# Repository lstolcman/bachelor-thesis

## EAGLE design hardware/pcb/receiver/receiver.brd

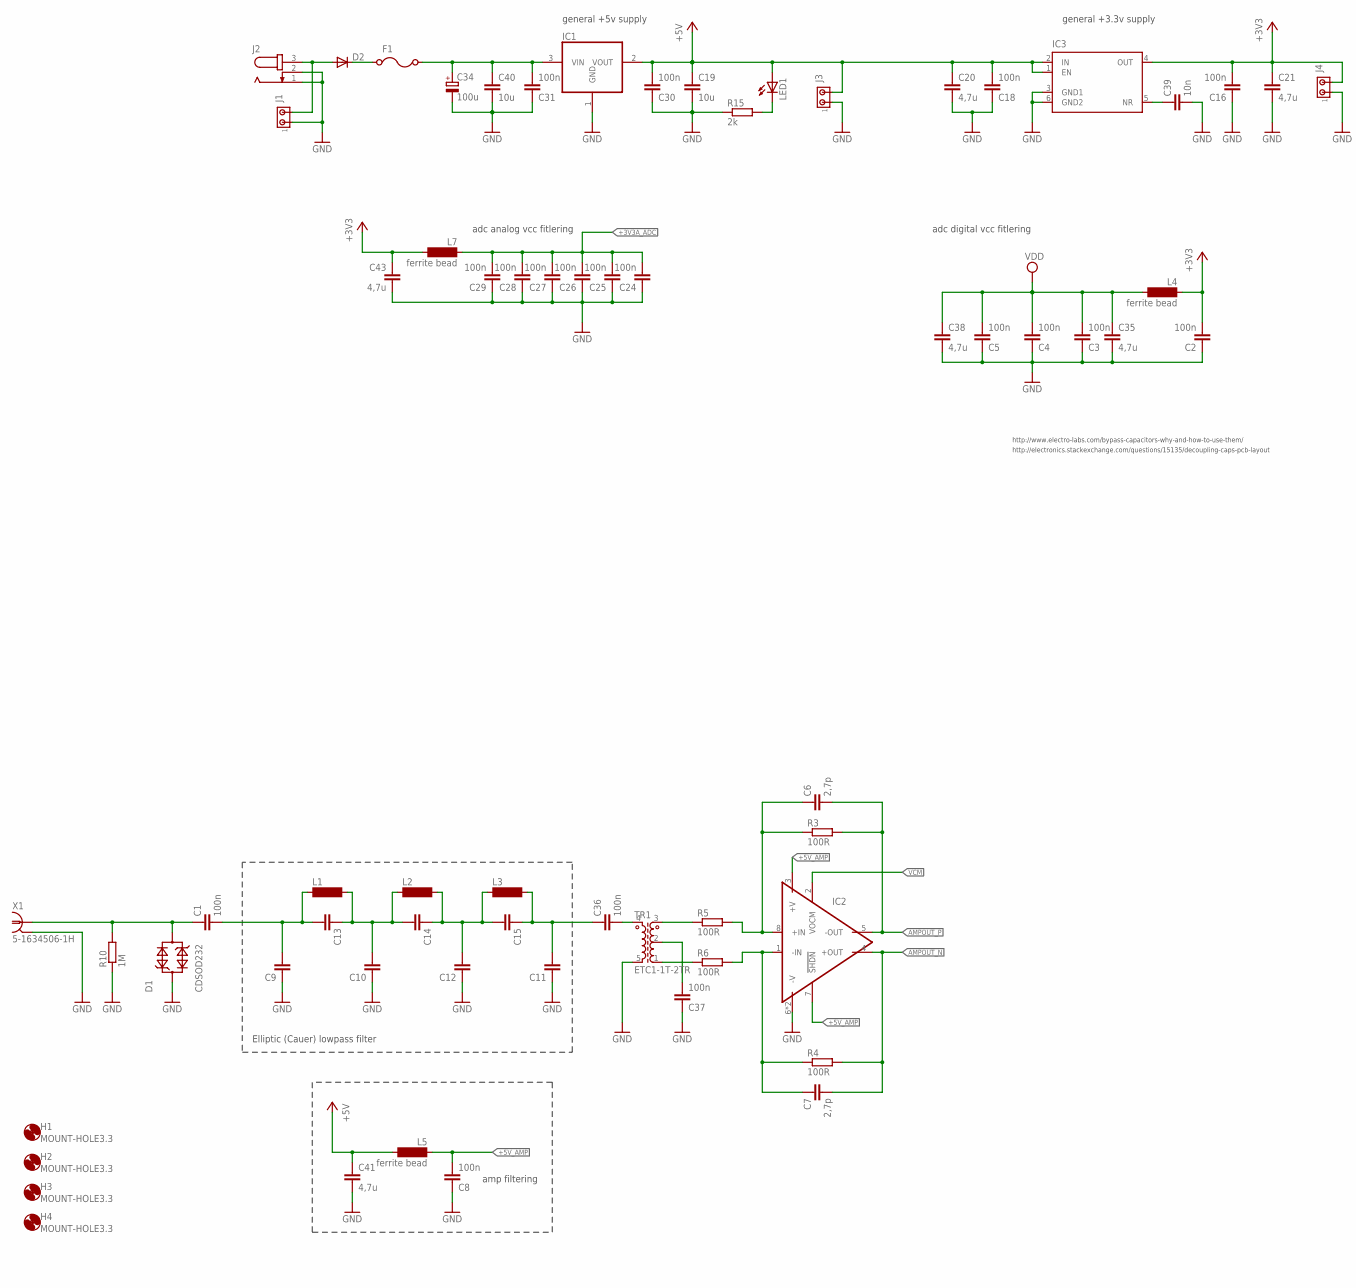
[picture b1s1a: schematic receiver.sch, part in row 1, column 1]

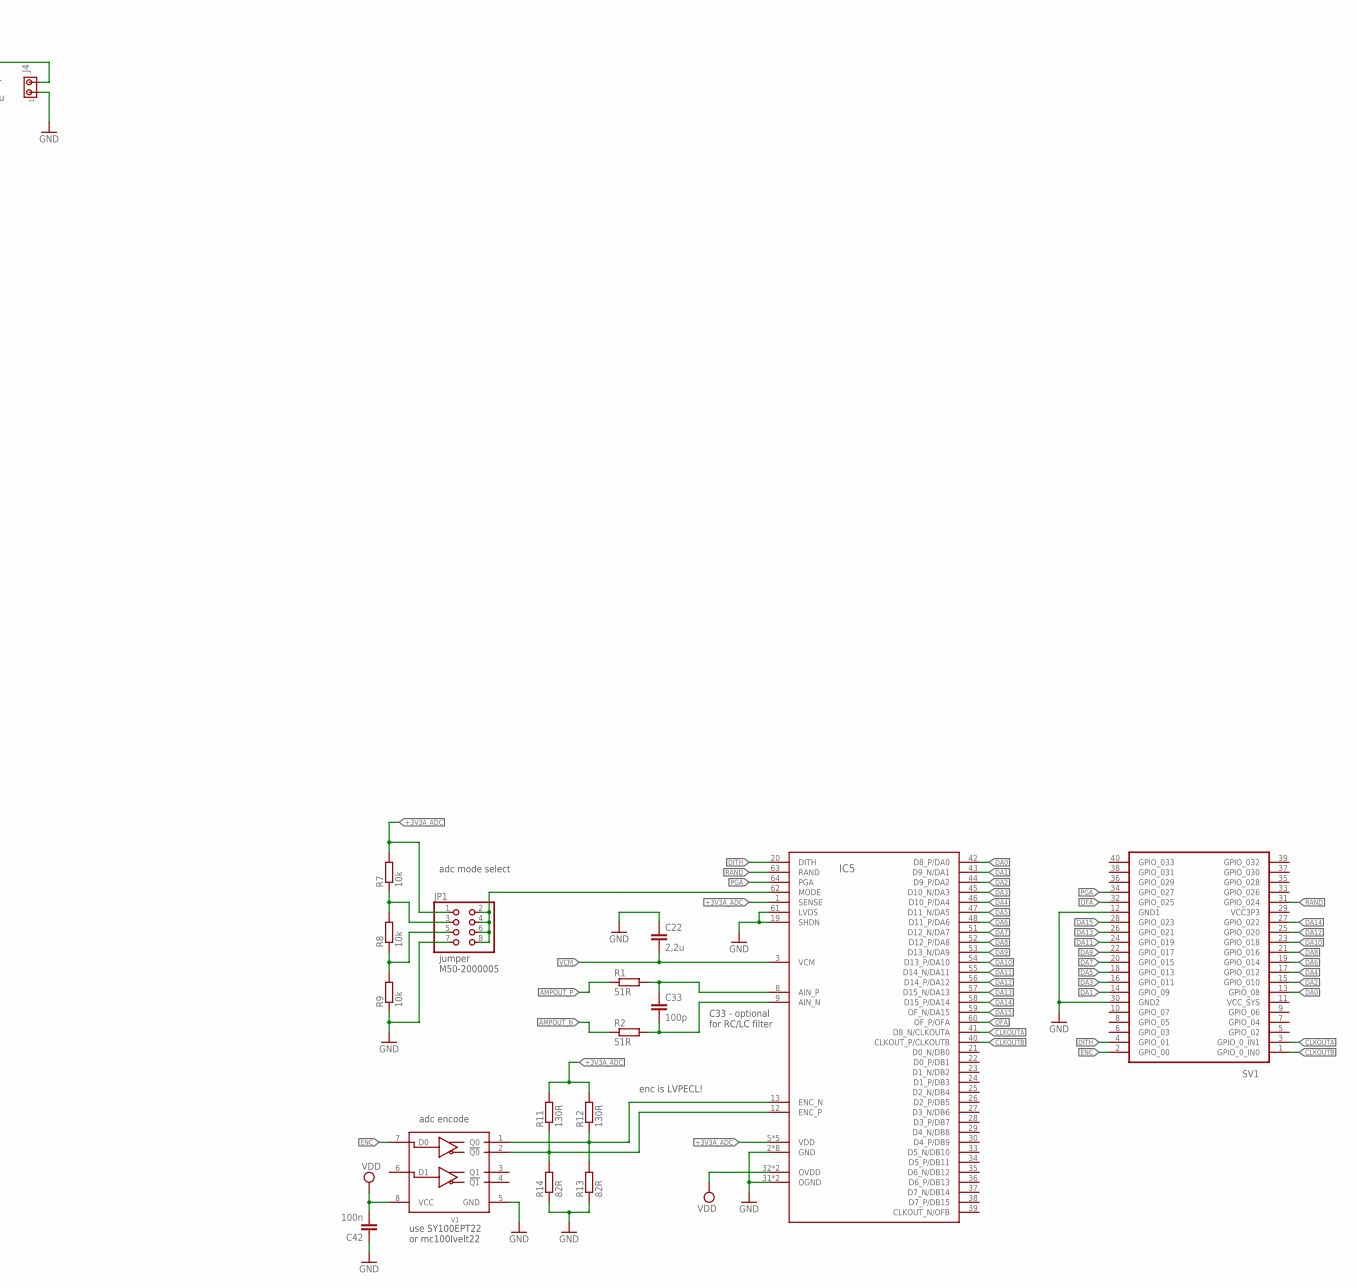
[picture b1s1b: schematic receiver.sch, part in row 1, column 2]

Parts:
C1, C2, C3, C4, C5, C8, C16, C18, C24, C25, C26, C27, C28, C29, C30, C31, C36, C37, C42: 100n; C0805
C6, C7: 2,7p; C0805
C9, C10, C11, C12, C13, C14, C15: C-EUC0805; C0805
C19, C40: 10u; C0805
C20, C21, C35, C38, C41, C43: 4,7u; C0805
C22: 2,2u; C0805
C33: 100p; C0805
C34: 100u; 153CLV-0605
C39: 10n; C0805
D1: CDSOD232; SOD323
D2: DIODE-DO214AC; DO214AC
F1: 0ZCG0150BF2C; CN1812
H1, H2, H3, H4: MOUNT-HOLE3.3; 3,3
IC1: REG1117; DPAK
IC2: LTC6405; MSOP8_TH
IC3: TPS73733; SOT223-6
IC5: LTC2208_FLAT; QFN64
J1, J3, J4: MTA02-100; 10X02MTA
J2: JACK-PLUG0; SPC4077
JP1: PINHD-2X4; 2X04_SMD
L1, L2, L3: SM-NE29
L4, L5, L7: ferrite bead; SM-NE29
LED1: LEDSML0805; SML0805
R1, R2: 51R; M0805
R3, R4, R5, R6: 100R; M0805
R7, R8, R9: 10k; M0805
R10: 1M; R0805
R11, R12: 130R; M1206
R13, R14: 82R; M1206
R15: 2k; M0805
SV1: PINHEADER; 2X20
TR1: ETC1-1T-2TR
V1: SY100EPT22; SOIC8
X1: 5-1634506-1H; 5-1634506-1

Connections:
12-18V: D2.A, J1.2, J2.3
+3V3: C2.2, C16.2, C21.1, C43.1, IC3.4 (OUT), J4.2, L4.1, L7.2
+3V3A_ADC: C24.2, C25.2, C26.2, C27.2, C28.2, C29.2, IC5.1 (SENSE), IC5.5 (VDD), IC5.6 (VDD), IC5.15 (VDD), IC5.16 (VDD), IC5.17 (VDD), JP1.1, L7.1, R7.2, R11.2, R12.2
+5V: C18.2, C19.1, C20.1, C30.2, C41.1, IC1.2 (VOUT), IC3.1 (EN), IC3.2 (IN), J3.2, L5.2, LED1.A
+5V_AMP: C8.2, IC2.3 (+V), IC2.7 (!SHDN), L5.1
AMPOUT_N: C7.2, IC2.4 (+OUT), R2.1, R4.2
AMPOUT_P: C6.2, IC2.5 (-OUT), R1.1, R3.2
CLKOUTA: IC5.41 (D8_N/CLKOUTA), SV1.3 (GPIO_0_IN1)
CLKOUTB: IC5.40 (CLKOUT_P/CLKOUTB), SV1.1 (GPIO_0_IN0)
DA0: IC5.42 (D8_P/DA0), SV1.13 (GPIO_08)
DA1: IC5.43 (D9_N/DA1), SV1.14 (GPIO_09)
DA2: IC5.44 (D9_P/DA2), SV1.15 (GPIO_010)
DA3: IC5.45 (D10_N/DA3), SV1.16 (GPIO_011)
DA4: IC5.46 (D10_P/DA4), SV1.17 (GPIO_012)
DA5: IC5.47 (D11_N/DA5), SV1.18 (GPIO_013)
DA6: IC5.48 (D11_P/DA6), SV1.19 (GPIO_014)
DA7: IC5.51 (D12_N/DA7), SV1.20 (GPIO_015)
DA8: IC5.52 (D12_P/DA8), SV1.21 (GPIO_016)
DA9: IC5.53 (D13_N/DA9), SV1.22 (GPIO_017)
DA10: IC5.54 (D13_P/DA10), SV1.23 (GPIO_018)
DA11: IC5.55 (D14_N/DA11), SV1.24 (GPIO_019)
DA12: IC5.56 (D14_P/DA12), SV1.25 (GPIO_020)
DA13: IC5.57 (D15_N/DA13), SV1.26 (GPIO_021)
DA14: IC5.58 (D15_P/DA14), SV1.27 (GPIO_022)
DA15: IC5.59 (OF_N/DA15), SV1.28 (GPIO_023)
DITH: IC5.20 (DITH), SV1.4 (GPIO_01)
ENC: SV1.2 (GPIO_00), V1.7 (D0)
ENC_N: IC5.12 (ENC_P), R11.1, R14.2, V1.2 (!Q0)
ENC_P: IC5.13 (ENC_N), R12.1, R13.2, V1.1 (Q0)
FILTERED_RF: C11.2, C15.1, C36.1, L3.2
GND: C2.1, C3.1, C4.1, C5.1, C8.1, C9.1, C10.1, C11.1, C12.1, C16.1, C18.1, C19.2, C20.2, C21.2, C22.1, C24.1, C25.1, C26.1, C27.1, C28.1, C29.1, C30.1, C31.1, C34.-, C35.2, C37.1, C38.2, C39.2, C40.2, C41.2, C42.1, C43.2, D1.1 (2), IC1.1 (GND), IC2.6 (-V), IC2.9 (-V), IC3.3 (GND1), IC3.6 (GND2), IC5.2 (GND), IC5.4 (GND), IC5.7 (GND), IC5.10 (GND), IC5.11 (GND), IC5.14 (GND), IC5.18 (GND), IC5.19 (SHDN), IC5.31 (OGND), IC5.50 (OGND), IC5.61 (LVDS), IC5.65 (GND), J1.1, J2.1, J2.2, J3.1, J4.1, JP1.7, R9.1, R10.1, R13.1, R14.1, R15.1, SV1.12 (GND1), SV1.30 (GND2), TR1.5, V1.5 (GND), X1.2, X1.3 (2), X1.4 (2), X1.5 (2)
IN_N: C33.2, IC5.9 (AIN_N), R2.2
IN_P: C33.1, IC5.8 (AIN_P), R1.2
MODE: IC5.62 (MODE), JP1.2, JP1.4, JP1.6, JP1.8
unnamed: R5.1, TR1.3
unnamed: C1.1, D1.2 (3), R10.2, X1.1
unnamed: C36.2, TR1.4
unnamed: C6.1, IC2.8 (+IN), R3.1, R5.2
unnamed: C7.1, IC2.1 (-IN), R4.1, R6.2
unnamed: JP1.3, R7.1, R8.2
unnamed: C31.2, C34.+, C40.1, F1.P$2 (2), IC1.3 (VIN)
unnamed: JP1.5, R8.1, R9.2
unnamed: LED1.C, R15.2
unnamed: D2.C, F1.P$1 (1)
unnamed: R6.1, TR1.1
unnamed: C37.2, TR1.2
unnamed: C1.2, C9.2, C13.2, L1.1
unnamed: C10.2, C13.1, C14.2, L1.2, L2.1
unnamed: C12.2, C14.1, C15.2, L2.2, L3.1
unnamed: C39.1, IC3.5 (NR)
OFA: IC5.60 (OF_P/OFA), SV1.32 (GPIO_025)
PGA: IC5.64 (PGA), SV1.34 (GPIO_027)
RAND: IC5.63 (RAND), SV1.31 (GPIO_024)
VCC3P3: SV1.29 (VCC3P3)
VCC_SYS: SV1.11 (VCC_SYS)
VCM: C22.2, IC2.2 (VOCM), IC5.3 (VCM)
VDD: C3.2, C4.2, C5.2, C35.1, C38.1, C42.2, IC5.32 (OVDD), IC5.49 (OVDD), L4.2, V1.8 (VCC)

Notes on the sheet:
Elliptic (Cauer) lowpass filter
adc analog vcc fitlering
adc mode select
enc is LVPECL!
use SY100EPT22 or mc100lvelt22
C33 - optional for RC/LC filter
general +5v supply
general +3.3v supply
http://www.electro-labs.com/bypass-capacitors-why-and-how-to-use-them/
amp filtering
http://electronics.stackexchange.com/questions/15135/decoupling-caps-pcb-layout
adc encode
jumper M50-2000005
adc digital vcc fitlering

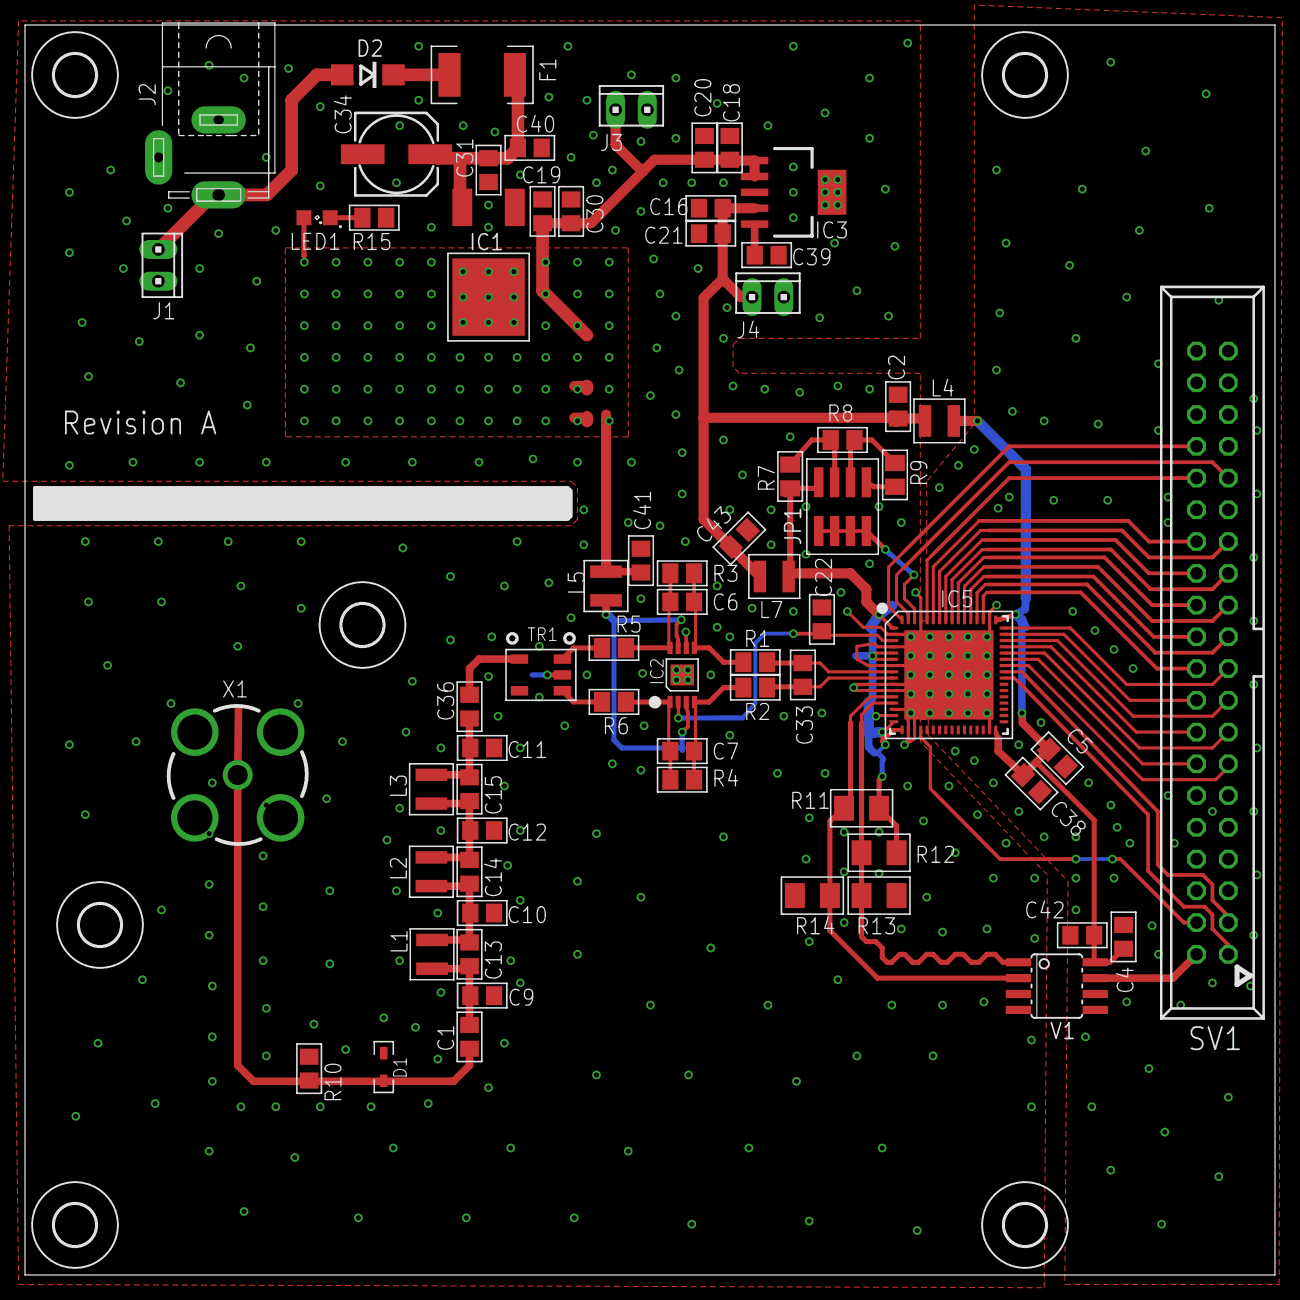
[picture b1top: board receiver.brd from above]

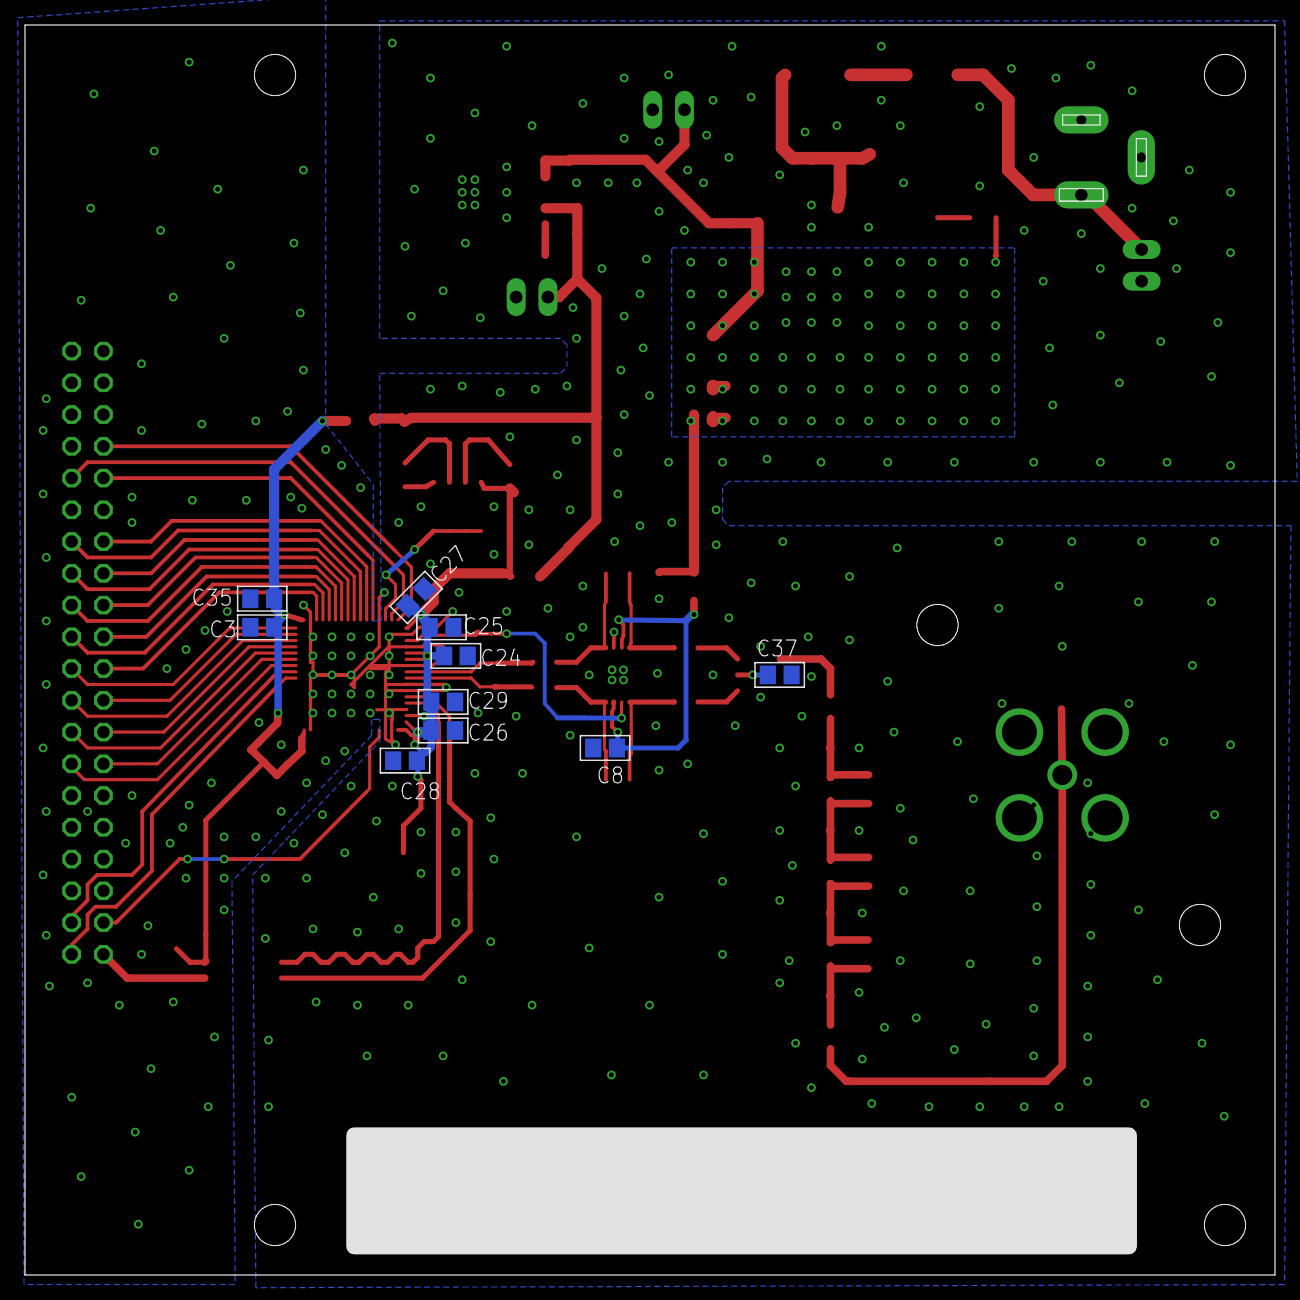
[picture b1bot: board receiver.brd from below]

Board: 2 copper layers, 100.0 x 100.0 mm, 84 parts (10 on the bottom side), 55 nets.

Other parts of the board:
H5, H6: MOUNT-HOLE3.3; 3,3@1

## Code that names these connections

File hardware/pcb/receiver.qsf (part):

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#============================================================
# GPIO_0, GPIO_0 connect to GPIO Default
#============================================================
set_location_assignment PIN_A8 -to CLKOUTB
set_instance_assignment -name IO_STANDARD "3.3-V LVTTL" -to CLKOUTB
set_location_assignment PIN_D3 -to ENC
set_instance_assignment -name IO_STANDARD "3.3-V LVTTL" -to ENC
set_location_assignment PIN_B8 -to CLKOUTA
set_instance_assignment -name IO_STANDARD "3.3-V LVTTL" -to CLKOUTA
set_location_assignment PIN_C3 -to DITH
set_instance_assignment -name IO_STANDARD "3.3-V LVTTL" -to DITH
set_location_assignment PIN_A2 -to gpio0[2]
set_instance_assignment -name IO_STANDARD "3.3-V LVTTL" -to gpio0[2]
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set_instance_assignment -name IO_STANDARD "3.3-V LVTTL" -to DA[14]
set_location_assignment PIN_E9 -to DA[15]
set_instance_assignment -name IO_STANDARD "3.3-V LVTTL" -to DA[15]
set_location_assignment PIN_C9 -to RAND
set_instance_assignment -name IO_STANDARD "3.3-V LVTTL" -to RAND
set_location_assignment PIN_D9 -to OFA
set_instance_assignment -name IO_STANDARD "3.3-V LVTTL" -to OFA
set_location_assignment PIN_E11 -to gpio0[26]
set_instance_assignment -name IO_STANDARD "3.3-V LVTTL" -to gpio0[26]
set_location_assignment PIN_E10 -to PGA
set_instance_assignment -name IO_STANDARD "3.3-V LVTTL" -to PGA
set_location_assignment PIN_C11 -to gpio0[28]
set_instance_assignment -name IO_STANDARD "3.3-V LVTTL" -to gpio0[28]
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#============================================================
# GPIO_1, GPIO_1 connect to GPIO Default
#============================================================
set_location_assignment PIN_T9 -to CLKOUTB
set_instance_assignment -name IO_STANDARD "3.3-V LVTTL" -to CLKOUTB
set_location_assignment PIN_F13 -to ENC
set_instance_assignment -name IO_STANDARD "3.3-V LVTTL" -to ENC
set_location_assignment PIN_R9 -to CLKOUTA
set_instance_assignment -name IO_STANDARD "3.3-V LVTTL" -to CLKOUTA
set_location_assignment PIN_T15 -to DITH
set_instance_assignment -name IO_STANDARD "3.3-V LVTTL" -to DITH
set_location_assignment PIN_T14 -to gpio1[2]
set_instance_assignment -name IO_STANDARD "3.3-V LVTTL" -to gpio1[2]
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set_instance_assignment -name IO_STANDARD "3.3-V LVTTL" -to DA[14]
set_location_assignment PIN_N16 -to DA[15]
set_instance_assignment -name IO_STANDARD "3.3-V LVTTL" -to DA[15]
set_location_assignment PIN_N15 -to RAND
set_instance_assignment -name IO_STANDARD "3.3-V LVTTL" -to RAND
set_location_assignment PIN_P14 -to OFA
set_instance_assignment -name IO_STANDARD "3.3-V LVTTL" -to OFA
set_location_assignment PIN_L14 -to gpio1[26]
set_instance_assignment -name IO_STANDARD "3.3-V LVTTL" -to gpio1[26]
set_location_assignment PIN_N14 -to PGA
set_instance_assignment -name IO_STANDARD "3.3-V LVTTL" -to PGA
set_location_assignment PIN_M10 -to gpio1[28]
set_instance_assignment -name IO_STANDARD "3.3-V LVTTL" -to gpio1[28]
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
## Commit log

2015-07-23 hw: add some doc about pa0rdt and pa0nhc antennas
2015-07-23 all: added files for antenna and doc
2015-10-10 hw: addded datasheets of ltc2208 ltc6405
2015-10-23 folder reorganization
2015-10-24 hw: pa0rdt & pa4nic combined in one schematic
2015-10-26 hw: added libs, modified receiver doc: added "proces dyplomowania" doc: added sample tex documents
2015-10-28 hw: misc changes, added fuses to power supply units
2015-10-28 hw: added n2adr sdr circuit as an example hw: added tvs diode to receiver
2015-10-28 hw: added n2adr hiqsdr code and diagrams
2015-10-28 hw: receiver power supply
2015-11-01 hw: added bibliography and hpsdr schematic hw: modified reciever - power supply
2015-11-01 hw: added filtering to adc hw: added mode switch to adc
2015-11-02 hw-receiver: added filter between amp and adc, minor changes
2015-11-02 hw: added doc about filtering digital and analog parts
2015-11-03 hw-receiver: created regions of power supply hw: added doc about decoupling
2015-11-04 hw: added lvttl to lvpecl enc inputs translator
2015-11-04 hw: added pullup pulldown resistors to lvpecl
2015-11-04 hw: grouped power supply
2015-11-04 hw: added Qucs project for adc anti-aliasing filter with simulation hw: added hpsdr images
2015-11-05 hw: added hermes pcb layout and bom
2015-11-05 hw: added manufacturer code for elements
2015-11-07 hw: added parts id to reciever
2015-11-14 hw: added bibliography, fitler for 55MHz cutoff
2015-11-14 hw: renaming bib files
2015-11-17 hw: changed receiver ferrite bead filters inductance to 600ohm
2015-11-23 hw: minor changes
2015-11-25 hw: bnc connector, misc changes
2015-11-27 hw: order list, receiver board schematic
2015-11-29 hw: receiver board changes
2015-11-30 hw: receiver ferrite beads between capacitors
2015-12-01 hw: elecrow DRC and drill rules updated
2015-12-01 hw: modified adc input clock resistors resistors
2015-12-02 hw: board updates
2015-12-02 hw: board
2015-12-03 hw: ground plane
2015-12-04 hw: added optional mta100
2015-12-04 hw: gnd vias
2015-12-04 hw: board misc changes
2015-12-04 hw: added some bibliography
2015-12-04 hw: board final touches
2015-12-04 hw: bibliography
2015-12-04 hw: final changes
2015-12-04 hw: First revision(revision A), cam file for Elecrow generated
2015-12-10 added bibliography entries
2015-12-11 doc: added writer2latex batch script to autocompile
2015-12-11 doc: changed odt to fodt to easier track changes by git
2015-12-11 doc: added polish cite sed replace in make
2015-12-11 doc: bibliography
2015-12-11 doc: sample text
2015-12-11 doc: correct interline and formatting
2015-12-20 sw: initial hdl code, pin assignments for quartus
2015-12-26 thesis: cfg: multilingual set to false (babel \selectlanguage errors)
2015-12-26 thesis: added polish dictionary checking to fodt files
2015-12-28 thesis: added documents from seminar
2015-12-28 added gitignores
2016-02-22 thesis: small cmf fixes, doc template
2016-02-22 thesis: cleanup, added bibliography
2016-02-22 thesis: removed makeidx, fixed hyperref for table of contents
2016-02-23 thesis: naming changes
2016-02-25 thesis: bibliography, intro
2016-02-25 thesis: added list to tex
2016-02-25 thesis: merged to one file
2016-02-25 thesis: removed unused files, make script
2016-02-26 thesis: update
2016-02-26 gitignore, added missing files
2016-02-29 thesis: added bib, fixed porzadki.pl
2016-02-29 thesis: porzadki.pl update, svg images initial
2016-03-01 thesis: added txt
2016-03-01 thesis: correct bibliography naming
2016-03-01 thesis: porzadki.pl original, working tables
2016-03-02 thesis: new text
2016-03-13 hw/sw: renamed CLKOUT_P/N naming to be the same as in datasheet
2016-03-13 sw: hdl SystemVerilog to Verilog option changed
2016-03-13 sw: hdl minimal working example
2016-04-12 software: template hdl project with proper fir filter coefficents
2016-04-12 software: hdl modules in separate directory
2016-04-12 software: hdl modules update, removed modelsim files
2016-04-12 software: hdl project updated - fir filters
2016-04-12 software: hdl modules - added dcf signal generator, altered sim scripts
2016-04-13 sw: hdl modules - removed reset circuitry
2016-04-14 sw: hdl and hdl modules edited
2016-04-14 doc: thesis acknowledgement and abstract, misc files
2016-04-14 sw: some simulation files in python
2016-04-14 doc: thesis images and scripts
2016-04-14 doc: thesis page numbering fixed
2016-04-15 doc: thesis appendixes, title page, acknoledgement, formatting etc
2016-04-16 doc: first chapter
2016-04-18 doc: thesis text updated
2016-04-19 doc: updated thesis
2016-04-19 doc: thesis update, software chapter
2016-04-20 doc: thesis sections update
2016-04-20 doc: thesis update
2016-04-25 sw: hdl_modules - goertzel altered, fully working goertzel simualtion works ok from second ready signal (first is incomplete because of incomplete samples)
2016-04-27 sw: goertzel analyzer python
2016-04-27 sw: simulation - python signal analyze script
2016-05-06 doc: thesis updated, corrected misc errors, 1st section
2016-05-08 doc: thesis - fixed itemize alignment, added abstract in english
2016-05-09 doc: thesis - added cic, uart subpars
2016-05-09 doc: added simulation images, modified diagrams, updated sections
2016-05-20 sw: fixed dcf77 generator
2016-05-20 sw: fixed dcf generator and reader
2016-05-20 sw: removed unnecessary module
2016-05-23 doc: thesis updated according to professor suggestions
2016-05-25 doc: added hw module architecture
2016-05-25 doc: thesis - added iamges of encoder and decoder
2016-05-25 sw: decoder and encoder code
2016-05-25 doc: thesis changed pcb physical drawing
2016-05-25 doc,sw: altered generators, added simulation images
2016-05-29 doc: changed thesis ending
2016-05-30 doc: modified location of table
2018-05-22 add missing files to git
